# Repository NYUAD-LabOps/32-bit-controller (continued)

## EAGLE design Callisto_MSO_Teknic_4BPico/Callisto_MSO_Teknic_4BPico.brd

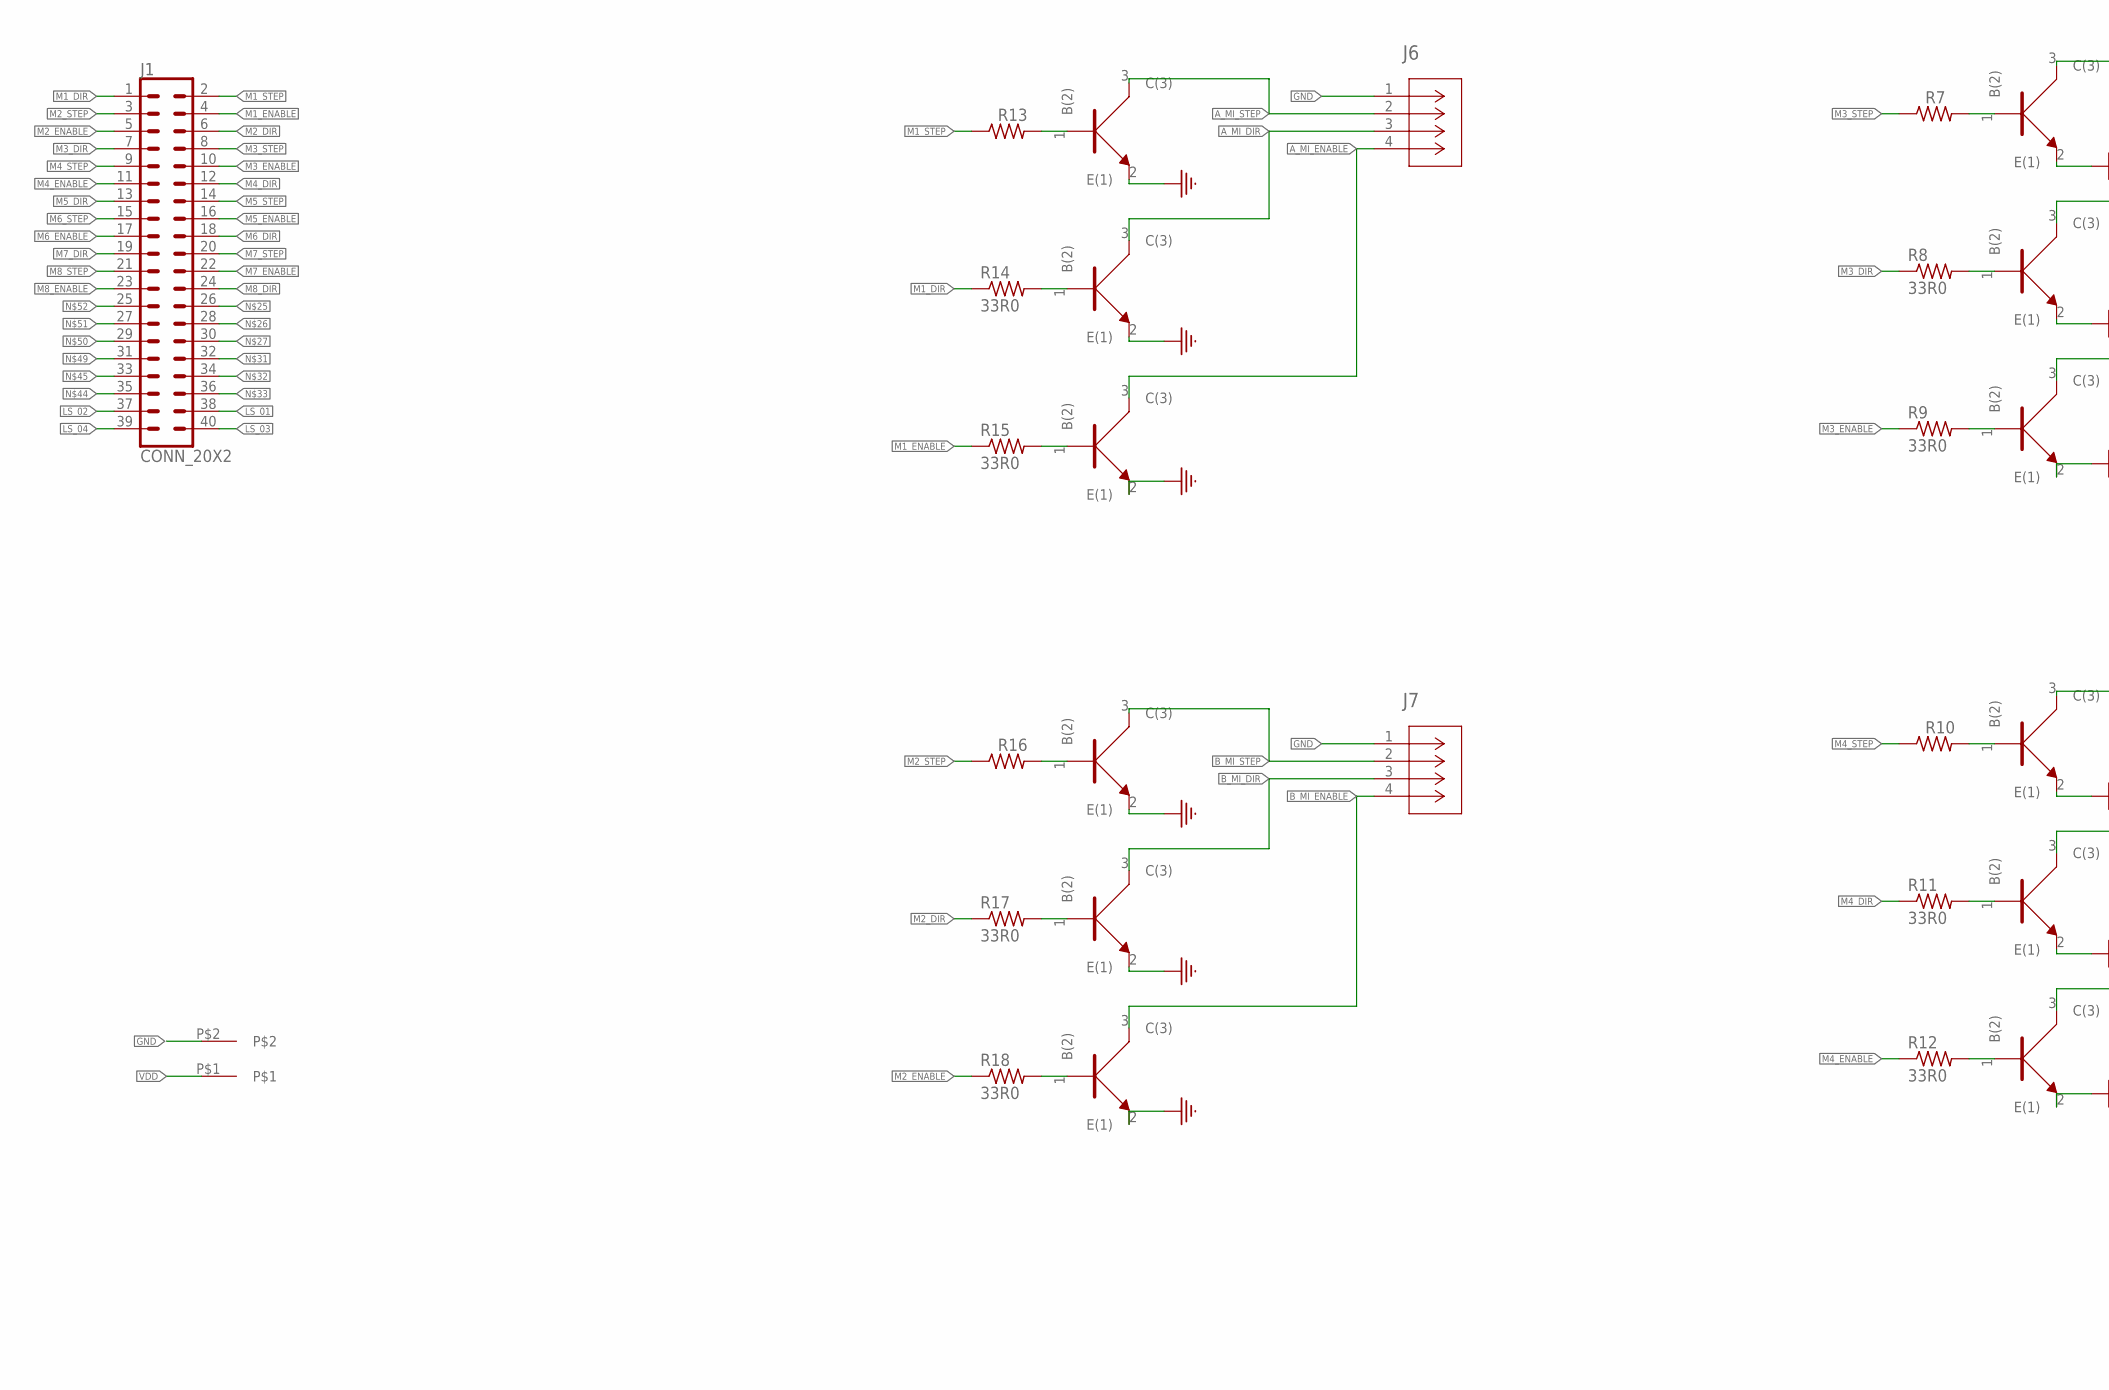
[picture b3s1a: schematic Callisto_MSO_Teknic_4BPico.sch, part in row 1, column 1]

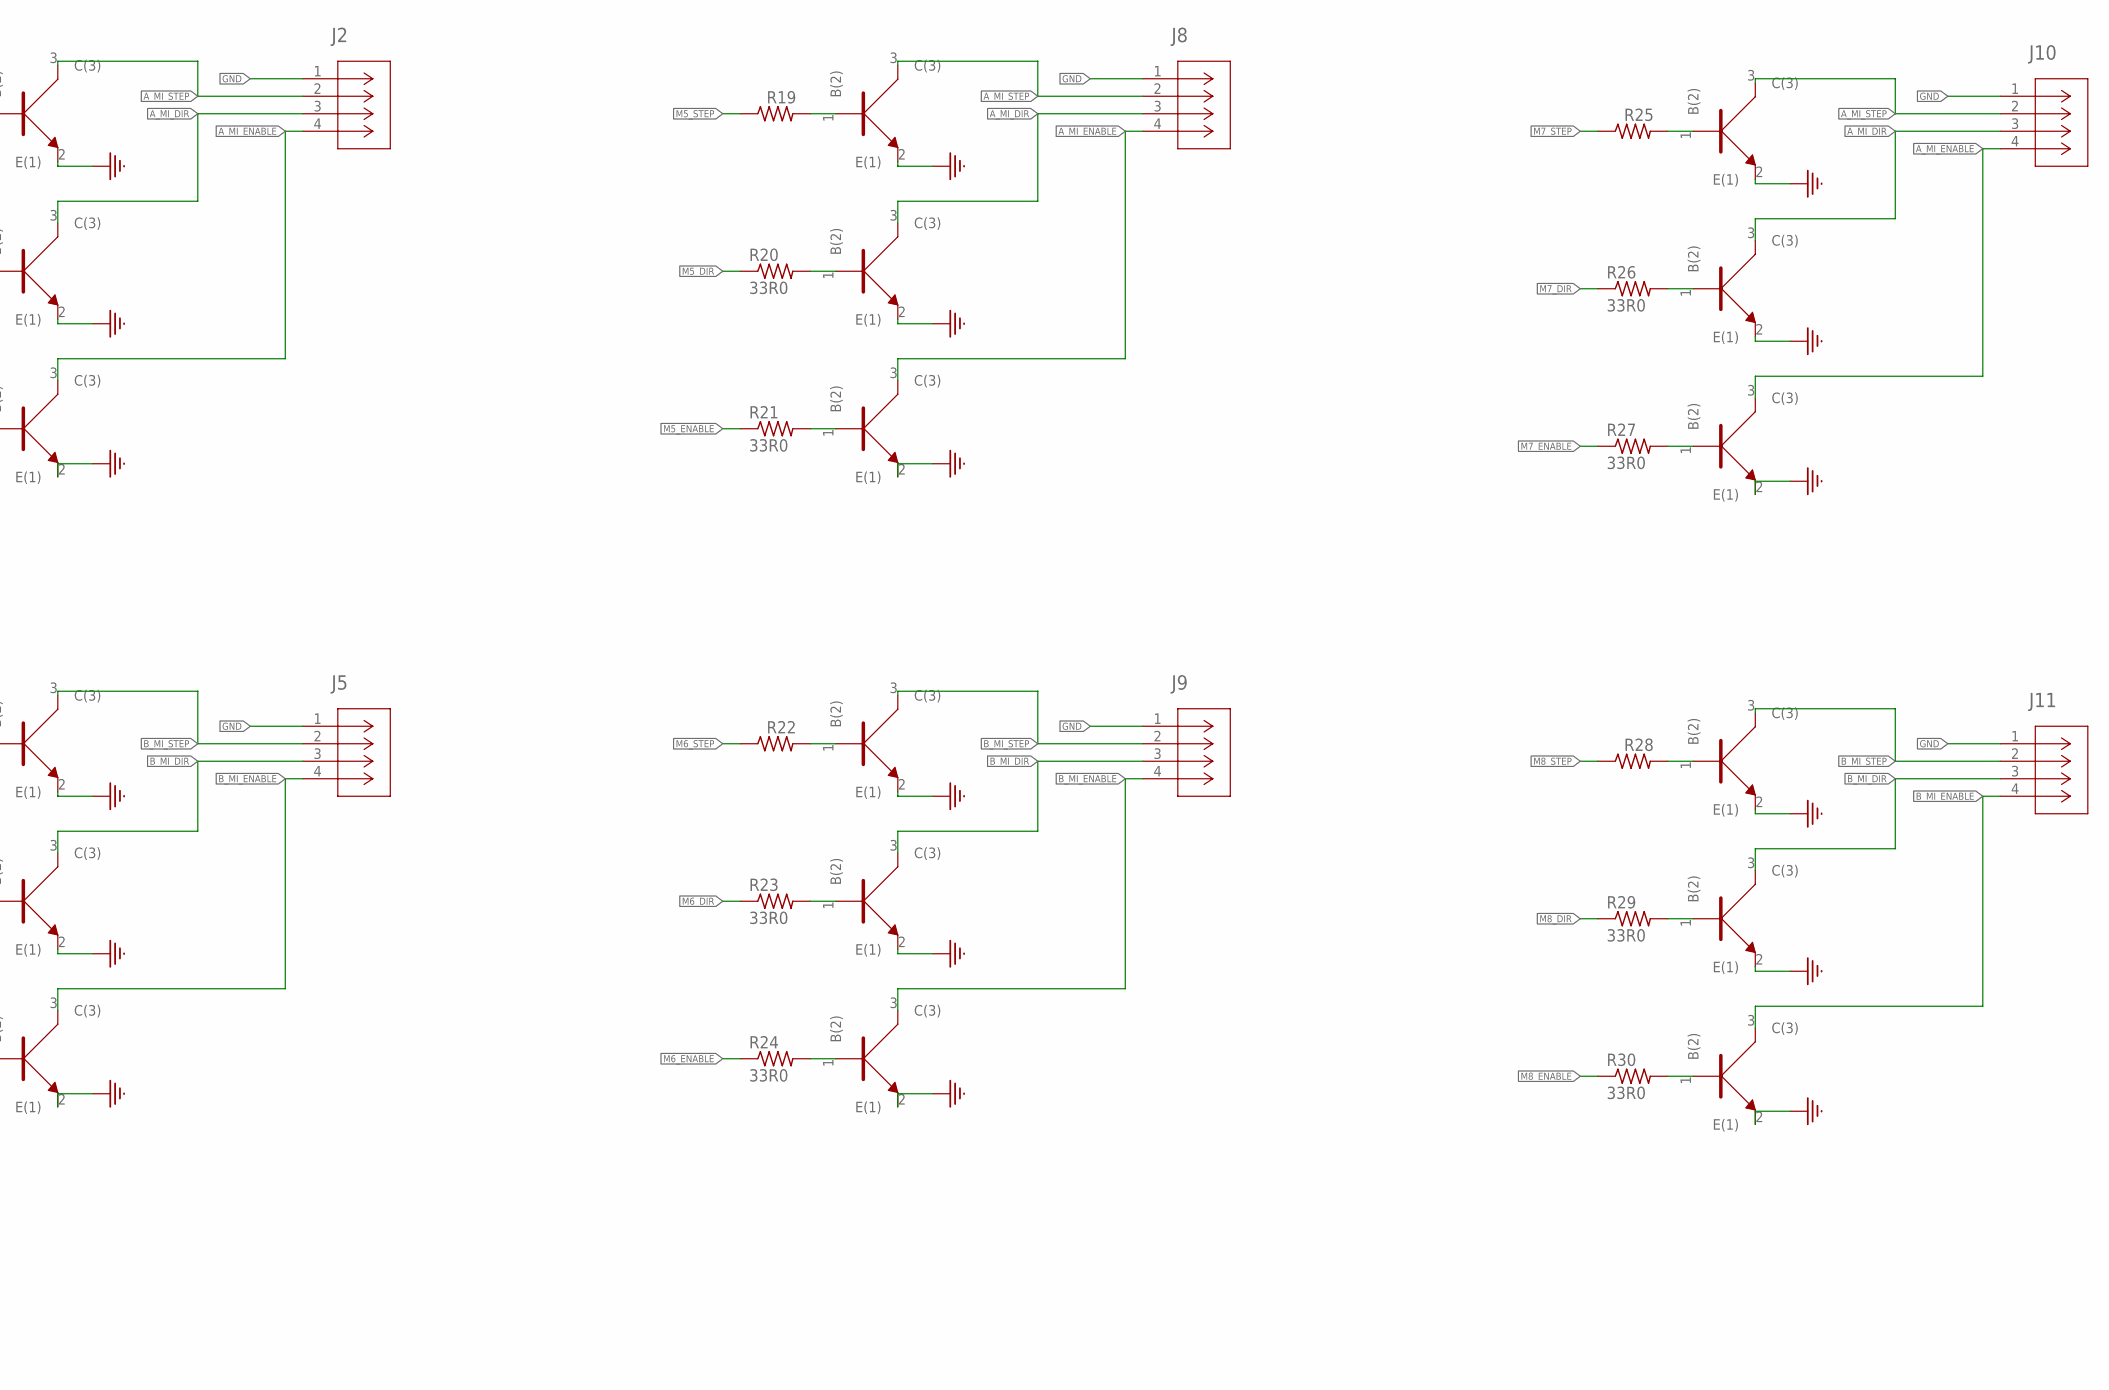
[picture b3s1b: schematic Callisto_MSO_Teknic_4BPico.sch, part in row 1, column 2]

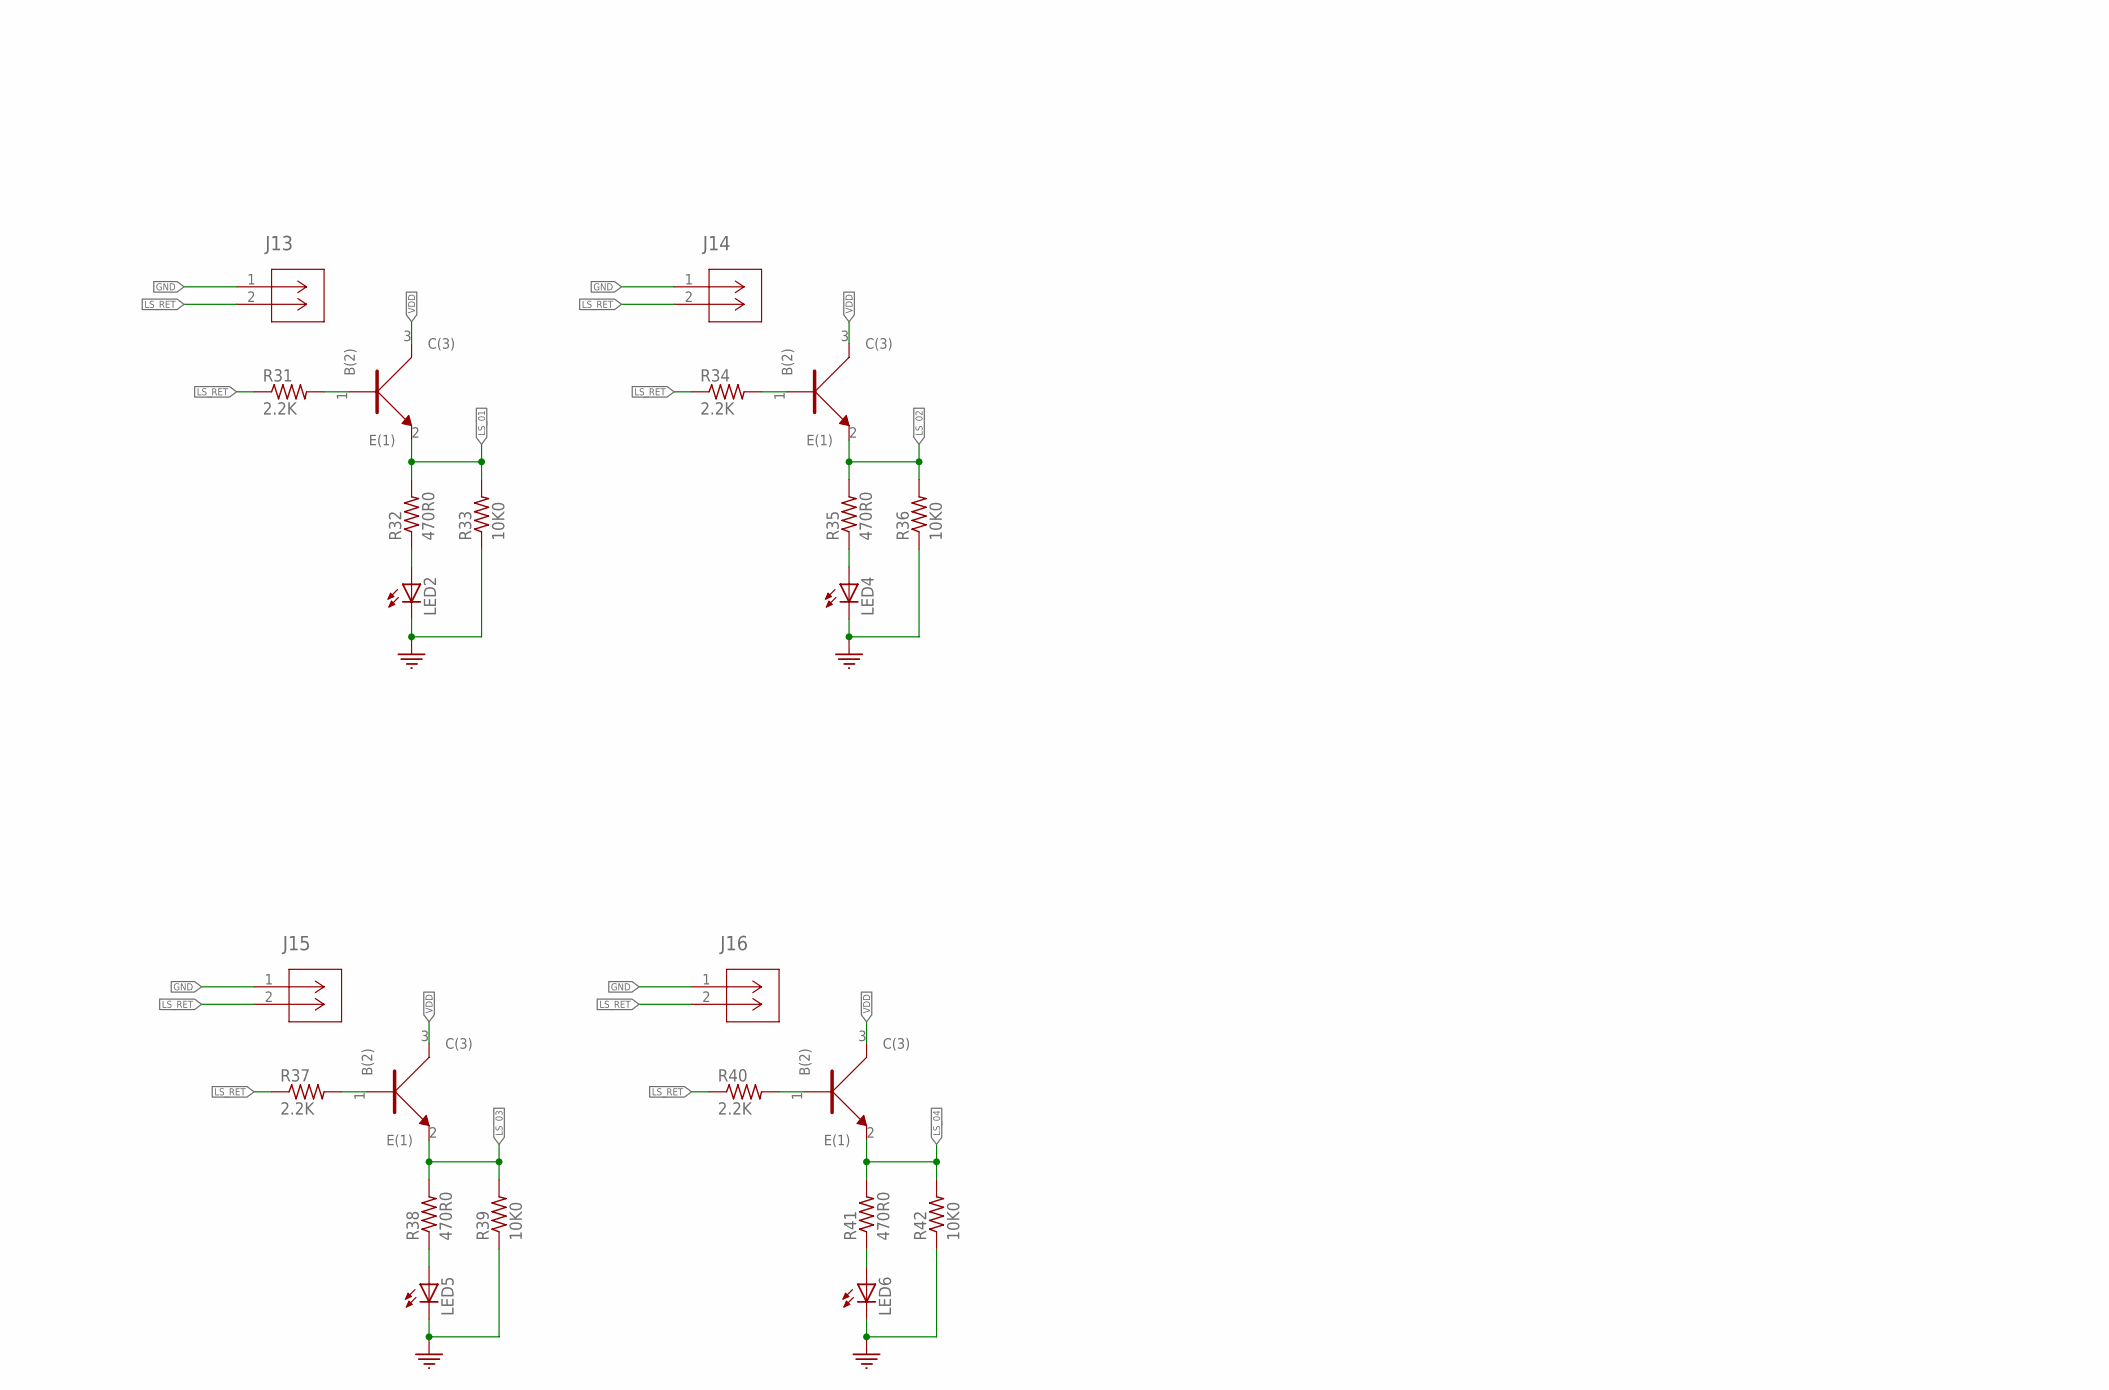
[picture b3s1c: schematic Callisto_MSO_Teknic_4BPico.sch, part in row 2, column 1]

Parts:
J1: CONN_20X2; 2X20
J2, J5, J6, J7, J8, J9, J10, J11: CONN_530470410_PICOBLADE_X_4; CON_530470410_MOL
J3: 2-pos; 2_3.81MM_PITCH
J13, J14, J15, J16: CONN_530470210_PICOBLADE_X_2; CON_530470210_MOL
LED2, LED4, LED5, LED6: Green; 0805
R7, R8, R9, R10, R11, R12, R13, R14, R15, R16, R17, R18, R19, R20, R21, R22, R23, R24, R25, R26, R27, R28, R29, R30: 33R0; 0402
R31, R34, R37, R40: 2.2K; 0402
R32, R35, R38, R41: 470R0; 0402
R33, R36, R39, R42: 10K0; 0402
U2, U4, U5, U6, U7, U8, U9, U10, U11, U12, U13, U14, U15, U16, U17, U18, U19, U20, U21, U22, U23, U24, U25, U26, U27, U28, U29, U30: NPN; SOT323

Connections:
A_MI_DIR: J2.3, J6.3, J8.3, J10.3, U8.3 (C(3)), U14.3 (C(3)), U20.3 (C(3)), U26.3 (C(3))
A_MI_ENABLE: J2.4, J6.4, J8.4, J10.4, U9.3 (C(3)), U15.3 (C(3)), U21.3 (C(3)), U27.3 (C(3))
A_MI_STEP: J2.2, J6.2, J8.2, J10.2, U7.3 (C(3)), U13.3 (C(3)), U19.3 (C(3)), U25.3 (C(3))
B_MI_DIR: J5.3, J7.3, J9.3, J11.3, U11.3 (C(3)), U17.3 (C(3)), U23.3 (C(3)), U29.3 (C(3))
B_MI_ENABLE: J5.4, J7.4, J9.4, J11.4, U12.3 (C(3)), U18.3 (C(3)), U24.3 (C(3)), U30.3 (C(3))
B_MI_STEP: J5.2, J7.2, J9.2, J11.2, U10.3 (C(3)), U16.3 (C(3)), U22.3 (C(3)), U28.3 (C(3))
GND: J2.1, J3.P$2, J5.1, J6.1, J7.1, J8.1, J9.1, J10.1, J11.1, J13.1, J14.1, J15.1, J16.1, LED2.2 (C), LED4.2 (C), LED5.2 (C), LED6.2 (C), R33.P$1 (1), R36.P$1 (1), R39.P$1 (1), R42.P$1 (1), U7.2 (E(1)), U8.2 (E(1)), U9.2 (E(1)), U10.2 (E(1)), U11.2 (E(1)), U12.2 (E(1)), U13.2 (E(1)), U14.2 (E(1)), U15.2 (E(1)), U16.2 (E(1)), U17.2 (E(1)), U18.2 (E(1)), U19.2 (E(1)), U20.2 (E(1)), U21.2 (E(1)), U22.2 (E(1)), U23.2 (E(1)), U24.2 (E(1)), U25.2 (E(1)), U26.2 (E(1)), U27.2 (E(1)), U28.2 (E(1)), U29.2 (E(1)), U30.2 (E(1))
LS_01: J1.38, R32.P$2 (2), R33.P$2 (2), U2.2 (E(1))
LS_02: J1.37, R35.P$2 (2), R36.P$2 (2), U4.2 (E(1))
LS_03: J1.40, R38.P$2 (2), R39.P$2 (2), U5.2 (E(1))
LS_04: J1.39, R41.P$2 (2), R42.P$2 (2), U6.2 (E(1))
LS_RET: J13.2, J14.2, J15.2, J16.2, R31.P$1 (1), R34.P$1 (1), R37.P$1 (1), R40.P$1 (1)
M1_DIR: J1.1, R14.P$1 (1)
M1_ENABLE: J1.4, R15.P$1 (1)
M1_STEP: J1.2, R13.P$1 (1)
M2_DIR: J1.6, R17.P$1 (1)
M2_ENABLE: J1.5, R18.P$1 (1)
M2_STEP: J1.3, R16.P$1 (1)
M3_DIR: J1.7, R8.P$1 (1)
M3_ENABLE: J1.10, R9.P$1 (1)
M3_STEP: J1.8, R7.P$1 (1)
M4_DIR: J1.12, R11.P$1 (1)
M4_ENABLE: J1.11, R12.P$1 (1)
M4_STEP: J1.9, R10.P$1 (1)
M5_DIR: J1.13, R20.P$1 (1)
M5_ENABLE: J1.16, R21.P$1 (1)
M5_STEP: J1.14, R19.P$1 (1)
M6_DIR: J1.18, R23.P$1 (1)
M6_ENABLE: J1.17, R24.P$1 (1)
M6_STEP: J1.15, R22.P$1 (1)
M7_DIR: J1.19, R26.P$1 (1)
M7_ENABLE: J1.22, R27.P$1 (1)
M7_STEP: J1.20, R25.P$1 (1)
M8_DIR: J1.24, R29.P$1 (1)
M8_ENABLE: J1.23, R30.P$1 (1)
M8_STEP: J1.21, R28.P$1 (1)
unnamed: R8.P$2 (2), U8.1 (B(2))
unnamed: R9.P$2 (2), U9.1 (B(2))
unnamed: R7.P$2 (2), U7.1 (B(2))
unnamed: R31.P$2 (2), U2.1 (B(2))
unnamed: LED2.1 (A), R32.P$1 (1)
unnamed: R11.P$2 (2), U11.1 (B(2))
unnamed: R12.P$2 (2), U12.1 (B(2))
unnamed: R10.P$2 (2), U10.1 (B(2))
unnamed: R14.P$2 (2), U14.1 (B(2))
unnamed: R15.P$2 (2), U15.1 (B(2))
unnamed: R13.P$2 (2), U13.1 (B(2))
unnamed: R17.P$2 (2), U17.1 (B(2))
unnamed: R18.P$2 (2), U18.1 (B(2))
unnamed: R16.P$2 (2), U16.1 (B(2))
unnamed: R20.P$2 (2), U20.1 (B(2))
unnamed: R21.P$2 (2), U21.1 (B(2))
unnamed: R19.P$2 (2), U19.1 (B(2))
unnamed: R23.P$2 (2), U23.1 (B(2))
unnamed: R24.P$2 (2), U24.1 (B(2))
unnamed: R22.P$2 (2), U22.1 (B(2))
unnamed: R26.P$2 (2), U26.1 (B(2))
unnamed: R27.P$2 (2), U27.1 (B(2))
unnamed: R25.P$2 (2), U25.1 (B(2))
unnamed: R29.P$2 (2), U29.1 (B(2))
unnamed: R30.P$2 (2), U30.1 (B(2))
unnamed: R28.P$2 (2), U28.1 (B(2))
unnamed: R34.P$2 (2), U4.1 (B(2))
unnamed: LED4.1 (A), R35.P$1 (1)
unnamed: R37.P$2 (2), U5.1 (B(2))
unnamed: LED5.1 (A), R38.P$1 (1)
unnamed: R40.P$2 (2), U6.1 (B(2))
unnamed: LED6.1 (A), R41.P$1 (1)
VDD: J3.P$1, U2.3 (C(3)), U4.3 (C(3)), U5.3 (C(3)), U6.3 (C(3))

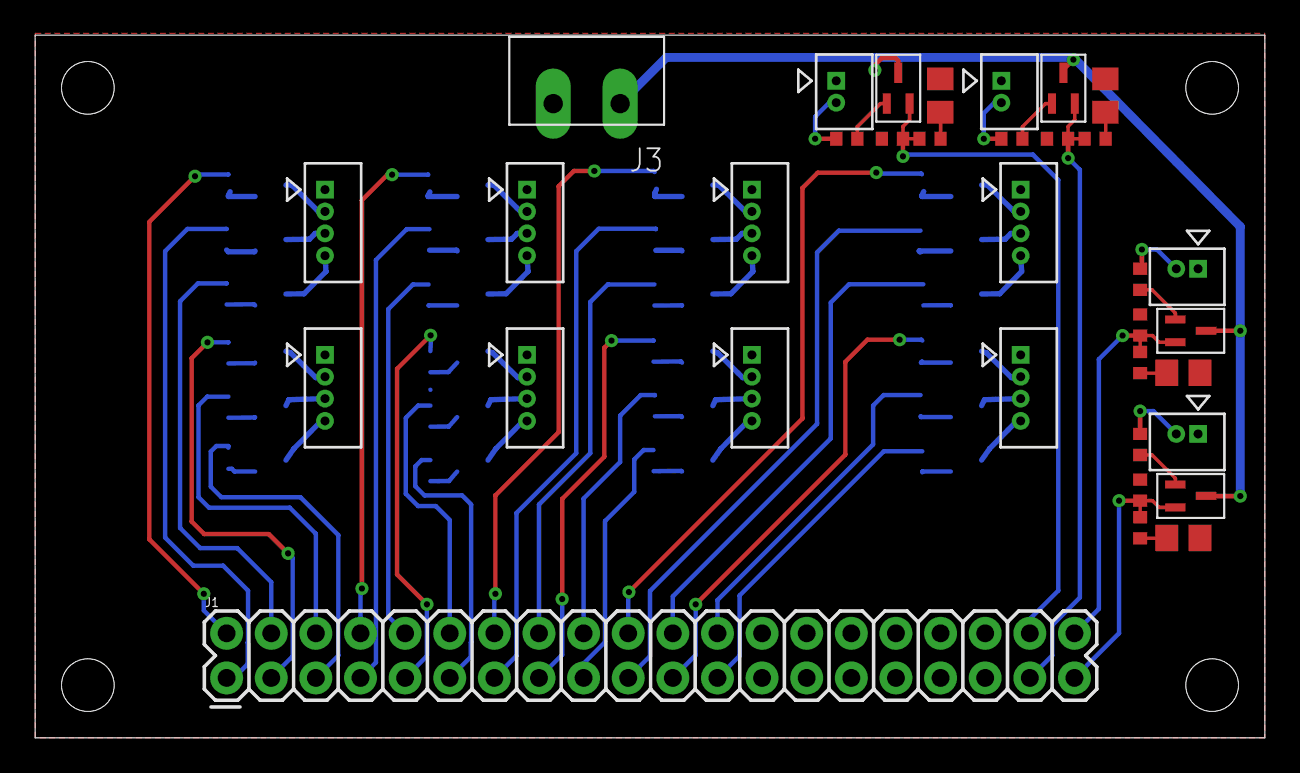
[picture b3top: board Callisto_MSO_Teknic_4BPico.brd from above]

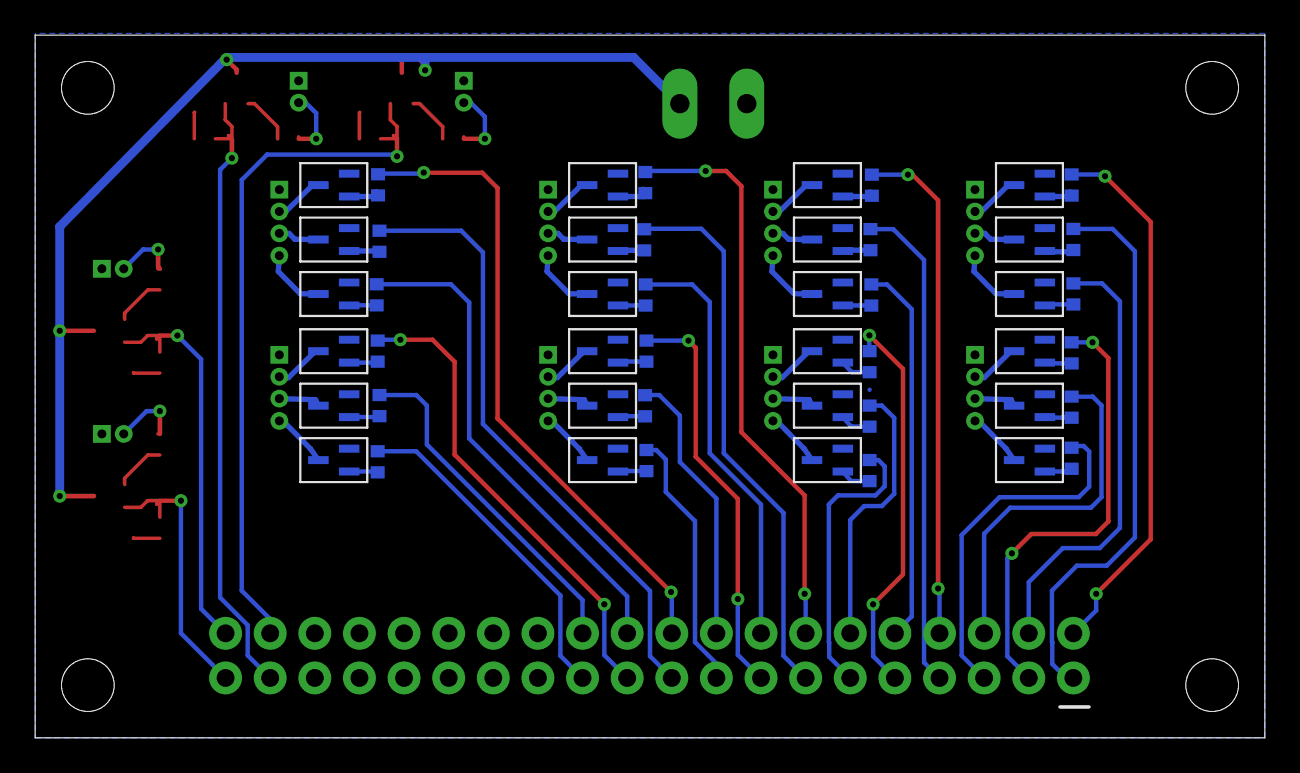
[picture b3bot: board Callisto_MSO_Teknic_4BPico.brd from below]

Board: 2 copper layers, 70.0 x 40.0 mm, 82 parts (48 on the bottom side), 69 nets.

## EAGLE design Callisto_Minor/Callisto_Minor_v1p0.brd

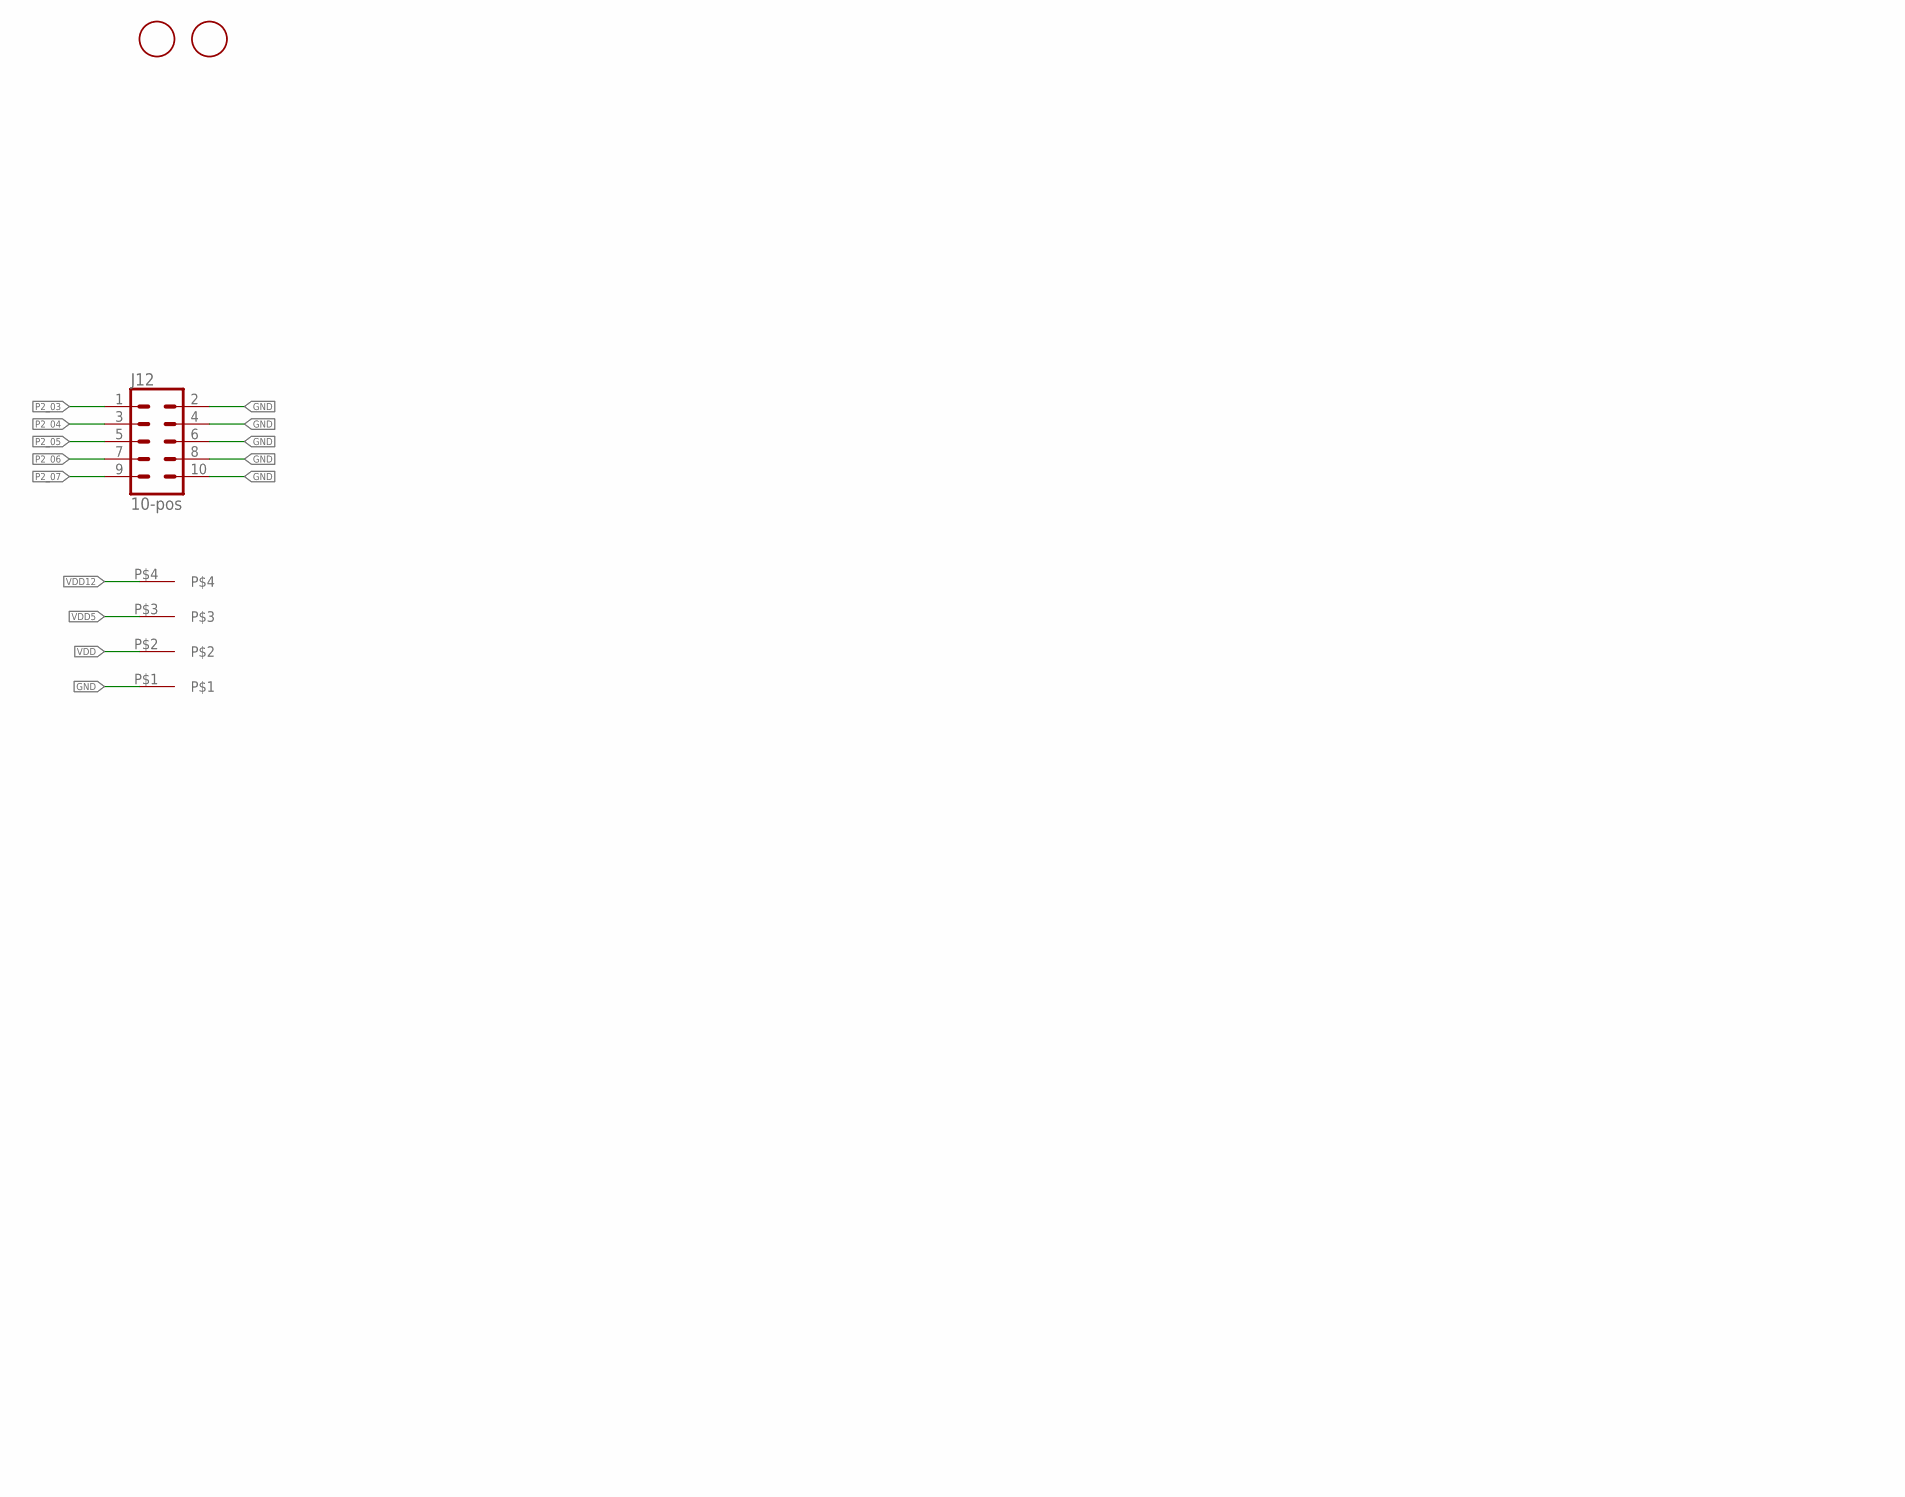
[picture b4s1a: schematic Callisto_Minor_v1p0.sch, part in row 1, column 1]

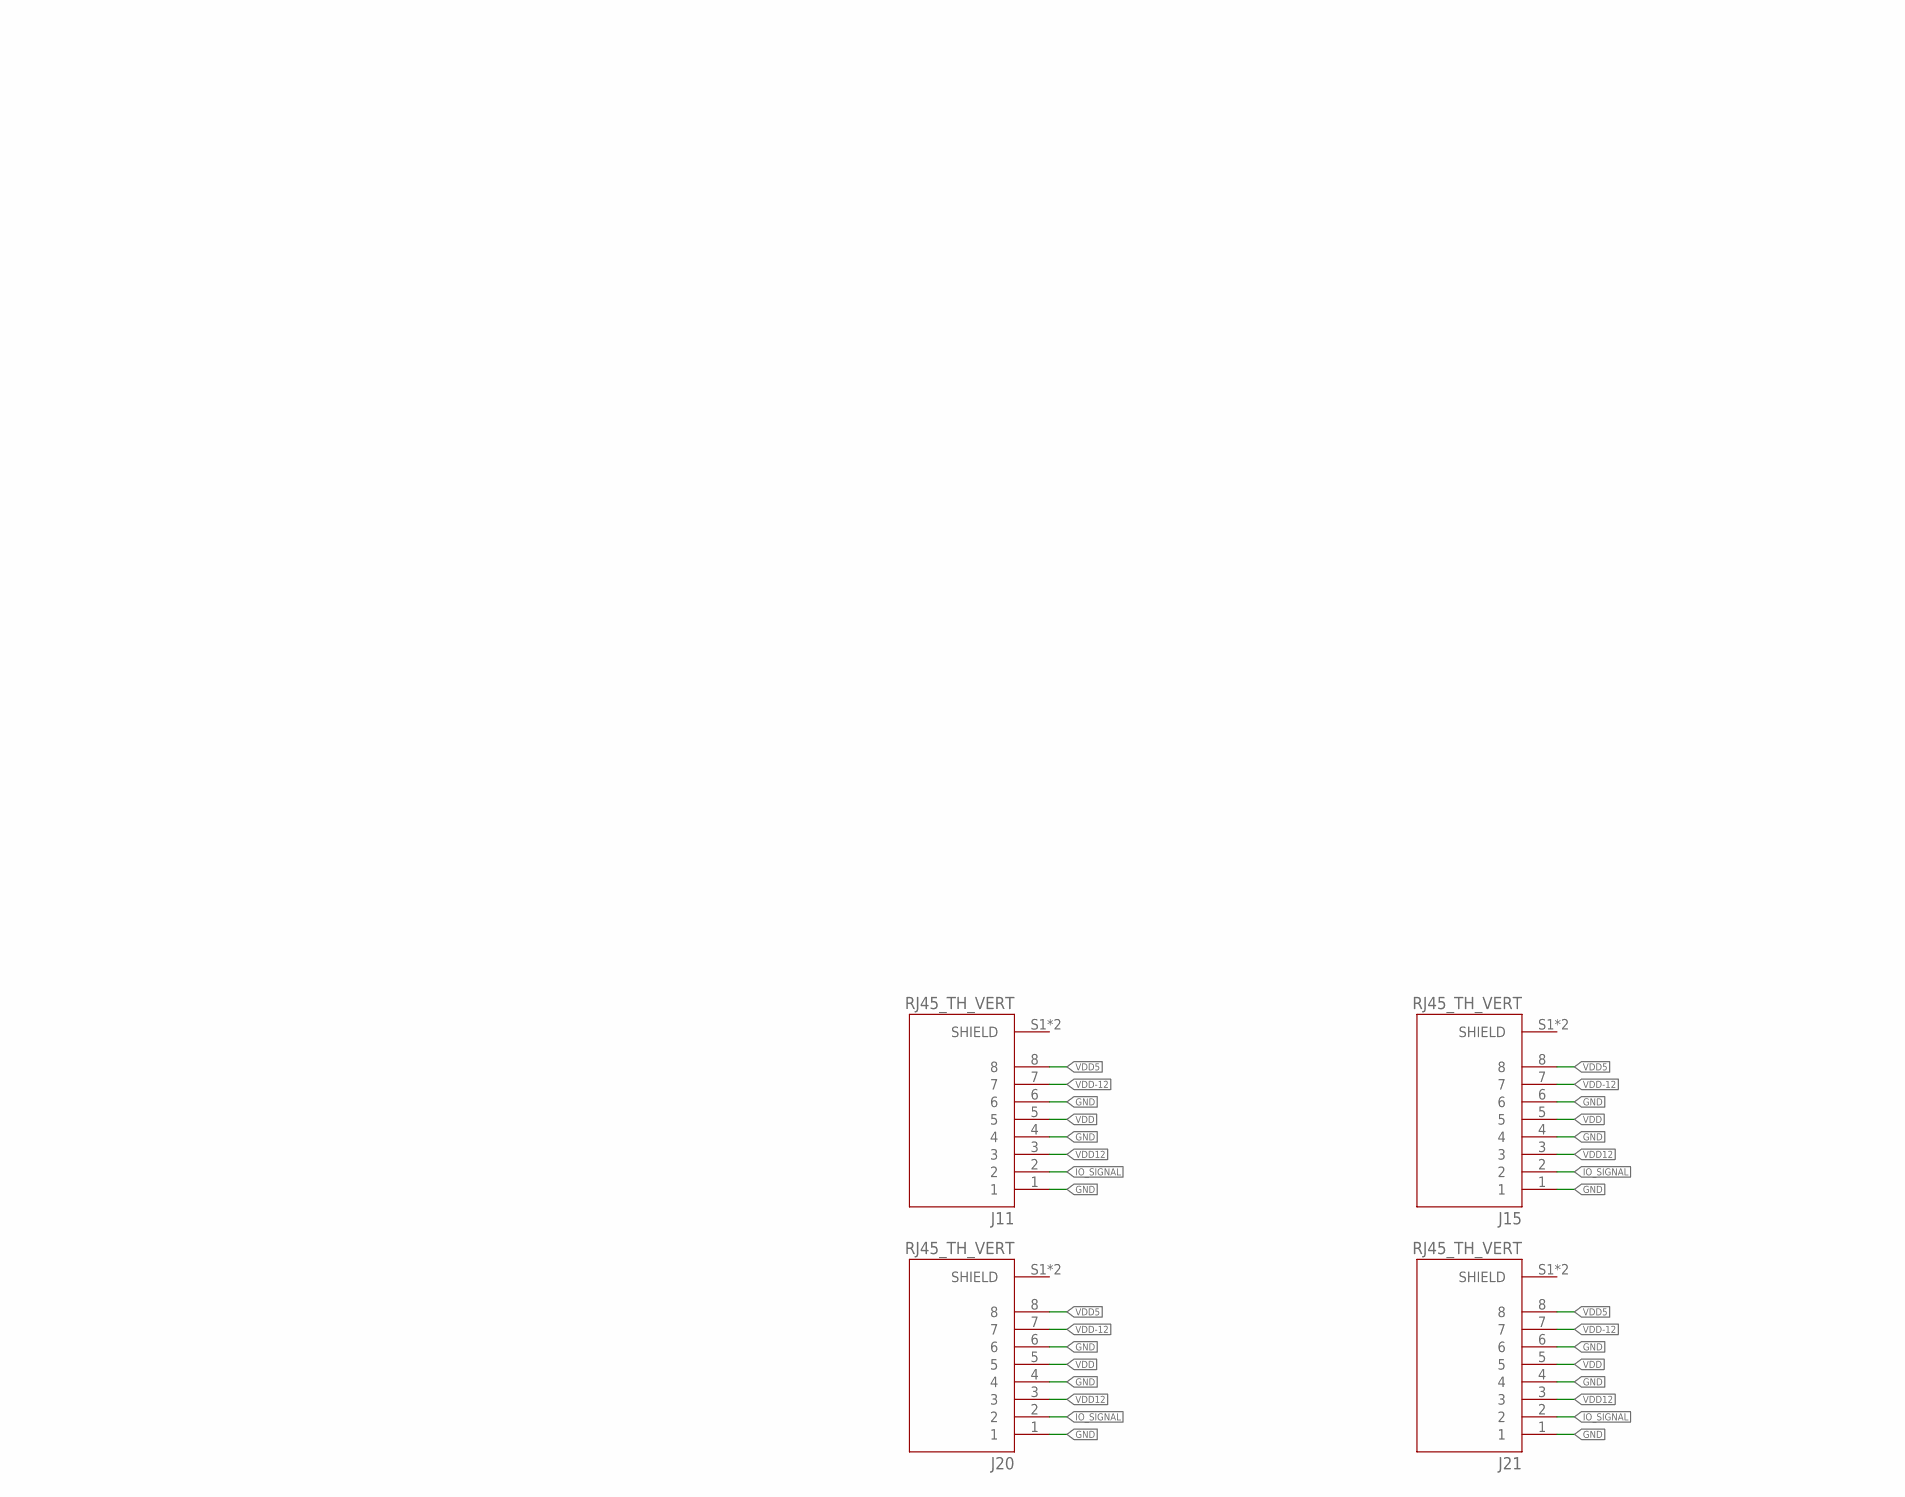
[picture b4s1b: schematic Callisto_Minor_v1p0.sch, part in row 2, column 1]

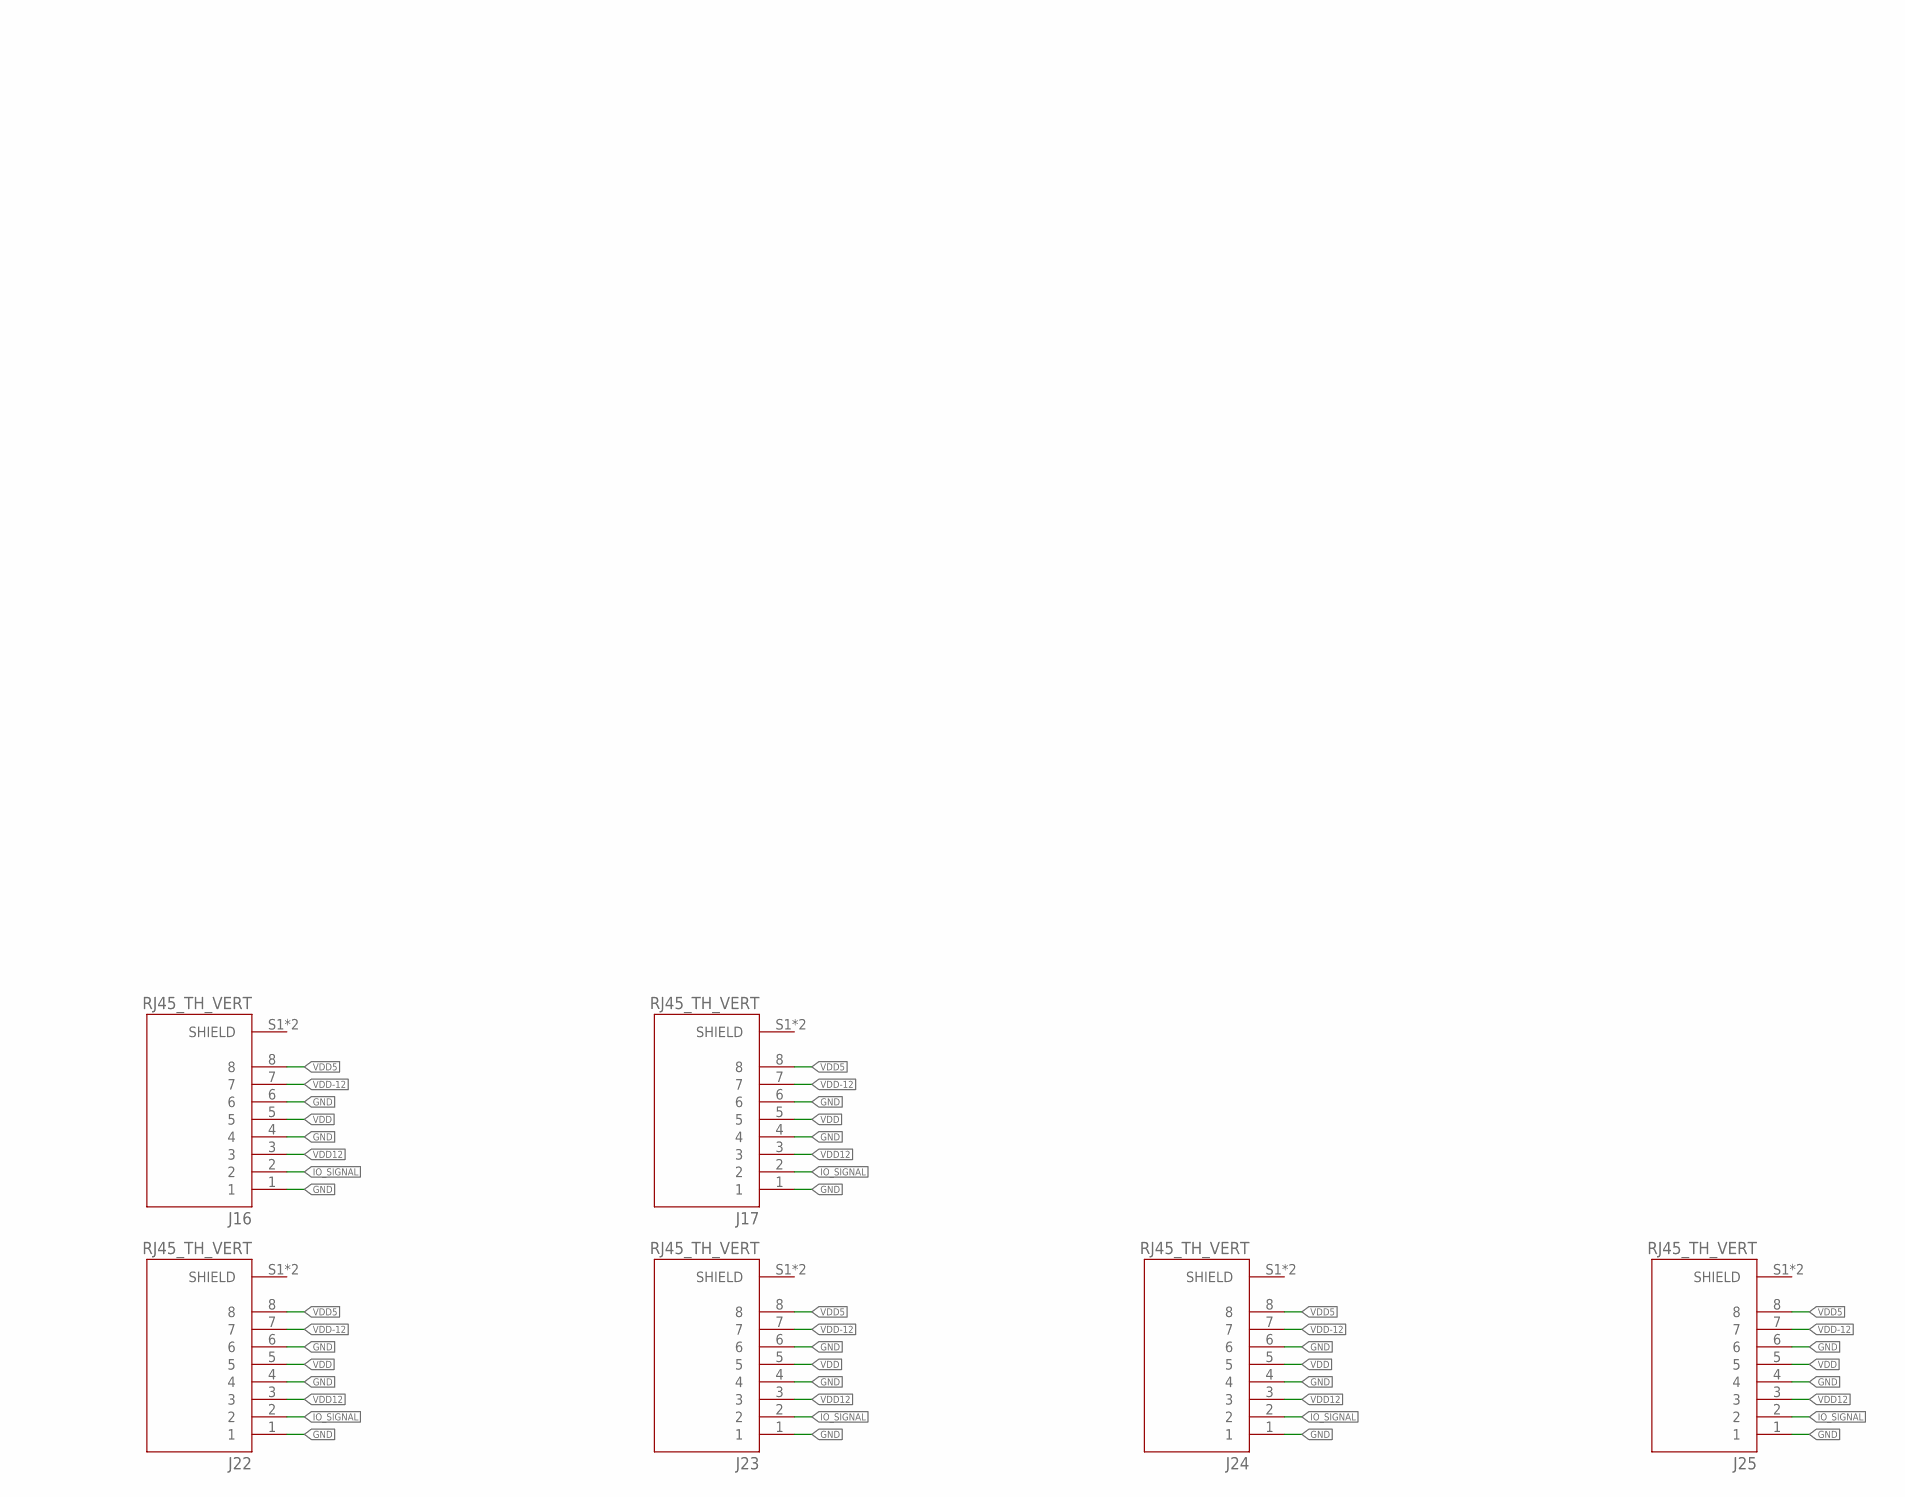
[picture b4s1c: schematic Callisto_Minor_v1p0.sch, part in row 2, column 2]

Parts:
J4: 4-pos; 1X4_3.81MM_PITCH
J11, J15, J16, J17, J20, J21, J22, J23, J24, J25: RJ45_TH_VERT; ASSMANN_A-2014-2S-4-N-R
J12: 10-pos; 2X5
U$1, U$2: FIDUCIAL_1MM

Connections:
GND: J4.P$1, J11.1, J11.4, J11.6, J12.2, J12.4, J12.6, J12.8, J12.10, J15.1, J15.4, J15.6, J16.1, J16.4, J16.6, J17.1, J17.4, J17.6, J20.1, J20.4, J20.6, J21.1, J21.4, J21.6, J22.1, J22.4, J22.6, J23.1, J23.4, J23.6, J24.1, J24.4, J24.6, J25.1, J25.4, J25.6
IO_SIGNAL: J11.2, J15.2, J16.2, J17.2, J20.2, J21.2, J22.2, J23.2, J24.2, J25.2
P2_03: J12.1
P2_04: J12.3
P2_05: J12.5
P2_06: J12.7
P2_07: J12.9
VDD: J4.P$2, J11.5, J15.5, J16.5, J17.5, J20.5, J21.5, J22.5, J23.5, J24.5, J25.5
VDD5: J4.P$3, J11.8, J15.8, J16.8, J17.8, J20.8, J21.8, J22.8, J23.8, J24.8, J25.8
VDD12: J4.P$4, J11.3, J15.3, J16.3, J17.3, J20.3, J21.3, J22.3, J23.3, J24.3, J25.3
VDD-12: J11.7, J15.7, J16.7, J17.7, J20.7, J21.7, J22.7, J23.7, J24.7, J25.7
